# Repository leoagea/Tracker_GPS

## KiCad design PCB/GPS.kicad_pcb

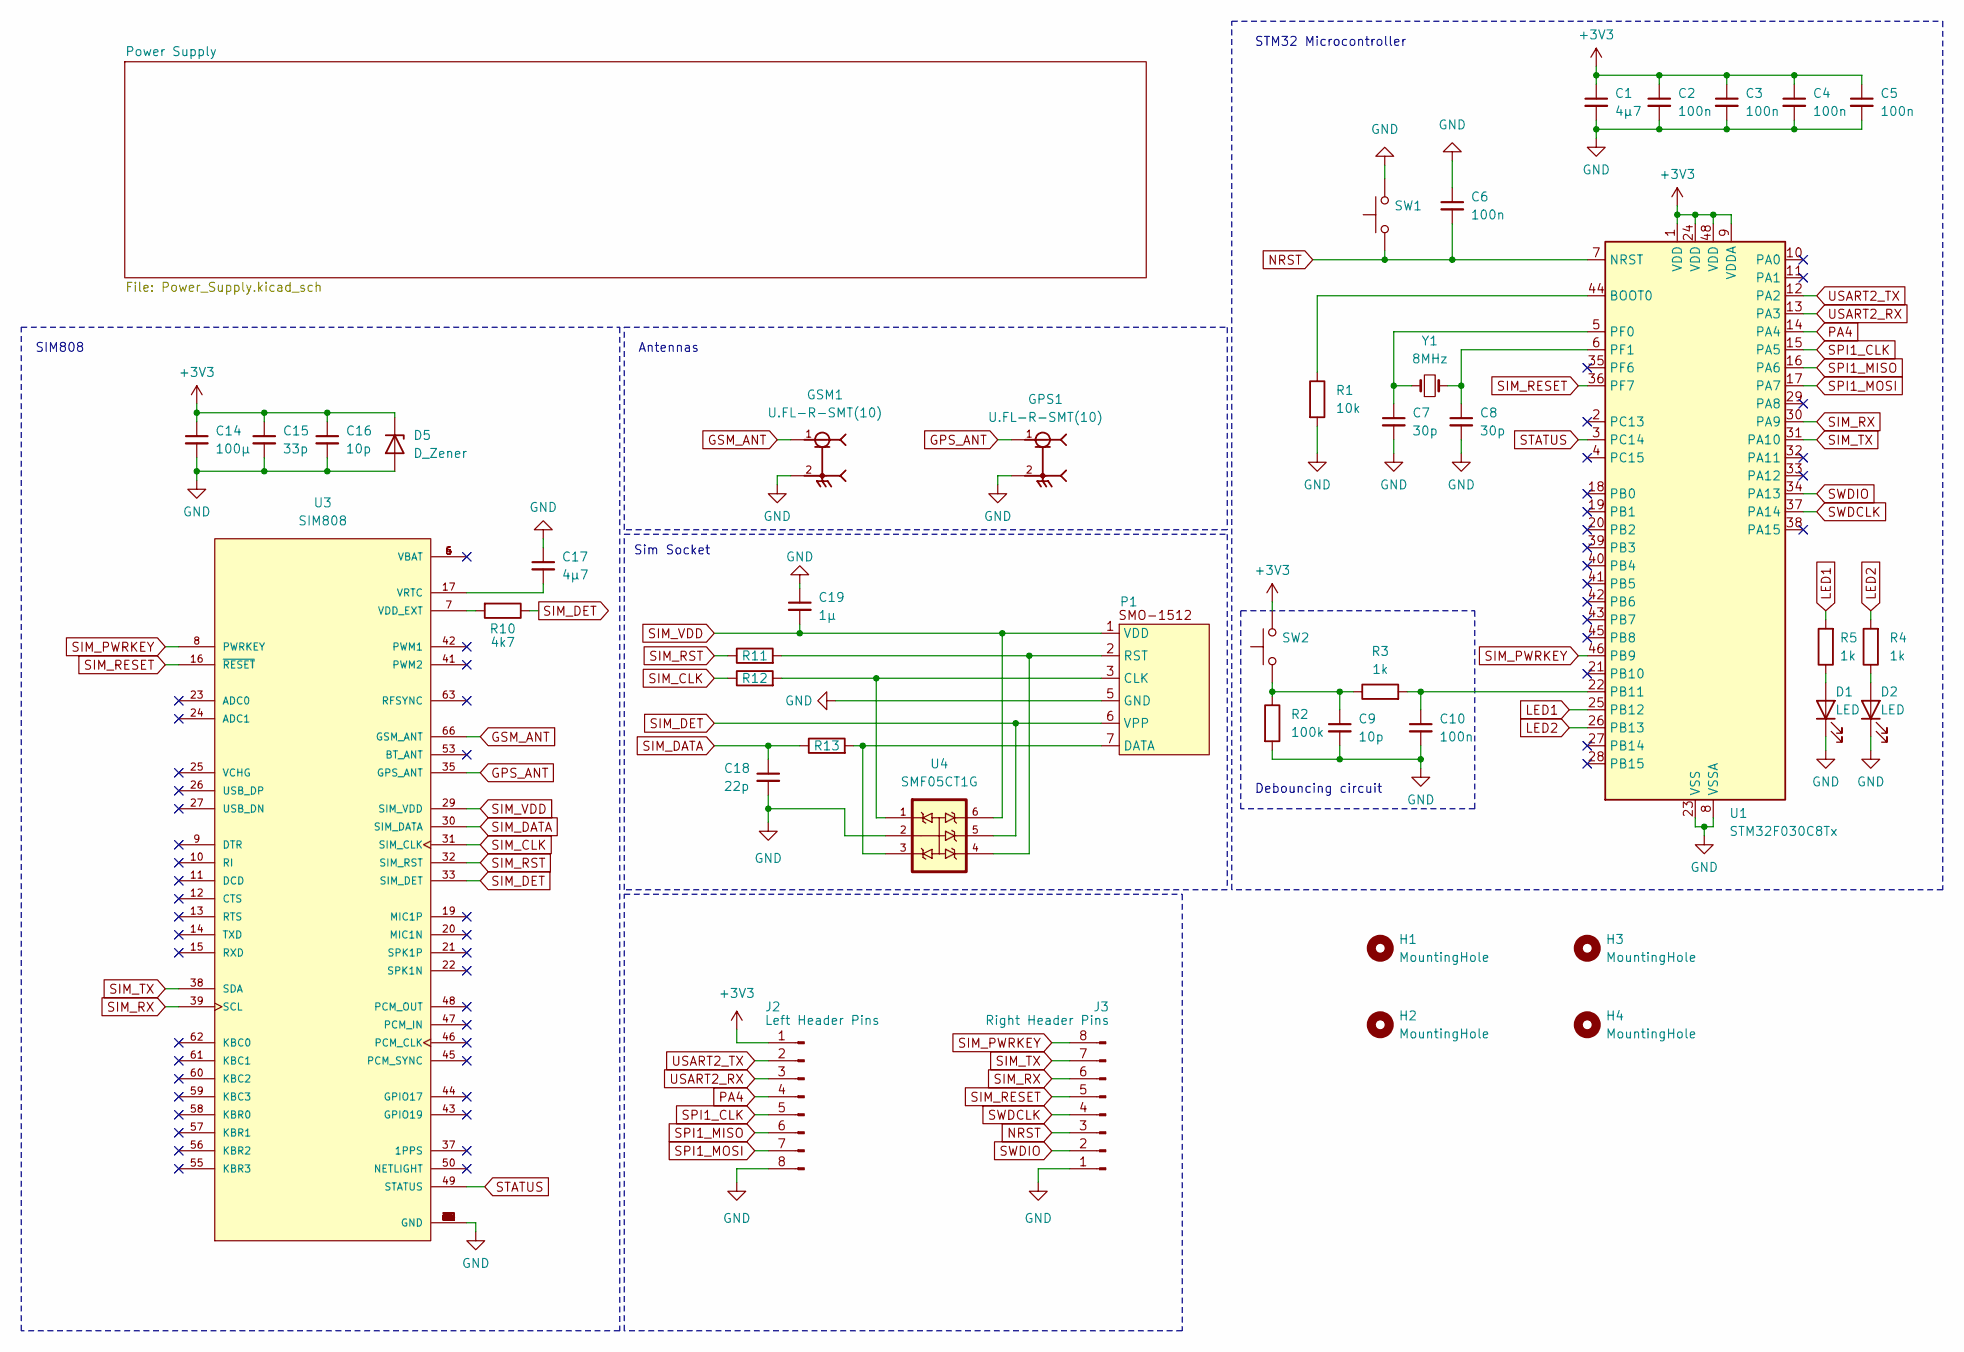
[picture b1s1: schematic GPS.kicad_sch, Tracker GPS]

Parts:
C1, C17: 4µ7; C_0603_1608Metric_Pad1.08x0.95mm_HandSolder; LCSC C19666
C2, C3, C4, C5, C6, C10: 100n; C_0402_1005Metric_Pad0.74x0.62mm_HandSolder; LCSC C1525
C7, C8: 30p; C_0402_1005Metric_Pad0.74x0.62mm_HandSolder; LCSC C1570
C9, C16: 10p; C_0402_1005Metric_Pad0.74x0.62mm_HandSolder; LCSC C32949
C14: 100µ; C_1206_3216Metric_Pad1.33x1.80mm_HandSolder; LCSC C15008
C15: 33p; C_0402_1005Metric_Pad0.74x0.62mm_HandSolder; LCSC C1562
C18: 22p; C_0402_1005Metric_Pad0.74x0.62mm_HandSolder; LCSC C1555
C19: 1µ; C_0402_1005Metric_Pad0.74x0.62mm_HandSolder; LCSC C52923
D1: LED; LED_0603_1608Metric_Pad1.05x0.95mm_HandSolder; LCSC C5151484
D2: LED; LED_0603_1608Metric_Pad1.05x0.95mm_HandSolder; LCSC C2286
D5: D_Zener; D_MiniMELF_Handsoldering; LCSC C2857190
GPS1: U.FL-R-SMT(10); U.FL_Hirose_U.FL-R-SMT-1_Vertical; LCSC C88373
GSM1: U.FL-R-SMT(10); U.FL_Hirose_U.FL-R-SMT-1_Vertical; LCSC C88373
H1, H2, H3, H4: MountingHole; MountingHole_2.5mm_Pad_Via
J2: Left Header Pins; PinHeader_1x08_P2.54mm_Vertical
J3: Right Header Pins; PinHeader_1x08_P2.54mm_Vertical
P1: SIM_CARD_SMO-1512; LCSC C125621
R1: 10k; R_01005_0402Metric_Pad0.57x0.30mm_HandSolder; LCSC C25744
R2: 100k; R_0201_0603Metric_Pad0.64x0.40mm_HandSolder; LCSC C25803
R3, R4, R5: 1k; R_0201_0603Metric_Pad0.64x0.40mm_HandSolder; LCSC C21190
R10: 4k7; R_0402_1005Metric_Pad0.72x0.64mm_HandSolder; LCSC C25900
R11, R12, R13: 22; R_01005_0402Metric_Pad0.57x0.30mm_HandSolder; LCSC C25092
SW1, SW2: SW_Push; XKB-TS-1187A; LCSC C318884
U1: STM32F030C8Tx; LQFP-48_7x7mm_P0.5mm; LCSC C23922
U3: SIM808; PARTREV 1.03; LCSC C126275
U4: SMF05CT1G; SOT-363_SC-70-6_Handsoldering; LCSC C15879
Y1: 8MHz; Crystal_SMD_5032-2Pin_5.0x3.2mm_HandSoldering; LCSC C115962

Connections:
+3V3: C1.1, C2.1, C3.1, C4.1, C5.1, C14.1, C15.1, C16.1, D5.1 (K), J2.1, SW2.2, U1.1 (VDD), U1.9 (VDDA), U1.24 (VDD), U1.48 (VDD); also elsewhere on the board
GND: C1.2, C2.2, C3.2, C4.2, C5.2, C6.1, C7.2, C8.2, C9.2, C10.2, C14.2, C15.2, C16.2, C17.1, C18.2, C19.1, D1.1 (K), D2.1 (K), D5.2 (A), GPS1.2, GSM1.2, J2.8, J3.1, P1.5 (GND), R1.2, R2.2, SW1.2, U1.8 (VSSA), U1.23 (VSS), U1.47 (VSS), U3.1 (GND), U3.2 (GND), U3.3 (GND), U3.18 (GND), U3.28 (GND), U3.34 (GND), U3.36 (GND), U3.40 (GND), U3.51 (GND), U3.52 (GND), U3.54 (GND), U3.64 (GND), U3.65 (GND), U3.67 (GND), U3.68 (GND), U4.2; also elsewhere on the board
GPS_ANT: GPS1.1, U3.35 (GPS_ANT)
GSM_ANT: GSM1.1, U3.66 (GSM_ANT)
LED1: R5.2, U1.25 (PB12)
LED2: R4.2, U1.26 (PB13)
NRST: C6.2, J3.3, SW1.1, U1.7 (NRST)
unnamed: C9.1, R2.1, R3.1, SW2.1
unnamed: D1.2 (A), R5.1
unnamed: D2.2 (A), R4.1
unnamed: P1.3 (CLK), R12.2, U4.1
unnamed: P1.7 (DATA), R13.2, U4.3
unnamed: P1.2 (RST), R11.2, U4.4
unnamed: R1.1, U1.44 (BOOT0)
unnamed: C10.1, R3.2, U1.22 (PB11)
unnamed: C7.1, U1.5 (PF0), Y1.1
unnamed: C8.1, U1.6 (PF1), Y1.2
unnamed: R10.2, U3.7 (VDD_EXT)
unnamed: C17.2, U3.17 (VRTC)
PA4: J2.4, U1.14 (PA4)
SIM_CLK: R12.1, U3.31 (SIM_CLK)
SIM_DATA: C18.1, R13.1, U3.30 (SIM_DATA)
SIM_DET: P1.6 (VPP), R10.1, U3.33 (SIM_DET), U4.5
SIM_PWRKEY: J3.8, U1.46 (PB9), U3.8 (PWRKEY)
SIM_RESET: J3.5, U1.36 (PF7), U3.16 (~RESET)
SIM_RST: R11.1, U3.32 (SIM_RST)
SIM_RX: J3.6, U1.30 (PA9), U3.39 (SCL)
SIM_TX: J3.7, U1.31 (PA10), U3.38 (SDA)
SIM_VDD: C19.2, P1.1 (VDD), U3.29 (SIM_VDD), U4.6
SPI1_CLK: J2.5, U1.15 (PA5)
SPI1_MISO: J2.6, U1.16 (PA6)
SPI1_MOSI: J2.7, U1.17 (PA7)
STATUS: U1.3 (PC14), U3.49 (STATUS)
SWDCLK: J3.4, U1.37 (PA14)
SWDIO: J3.2, U1.34 (PA13)
USART2_RX: J2.3, U1.13 (PA3)
USART2_TX: J2.2, U1.12 (PA2)

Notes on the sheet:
Antennas
Sim Socket
Debouncing circuit
SIM808
STM32 Microcontroller

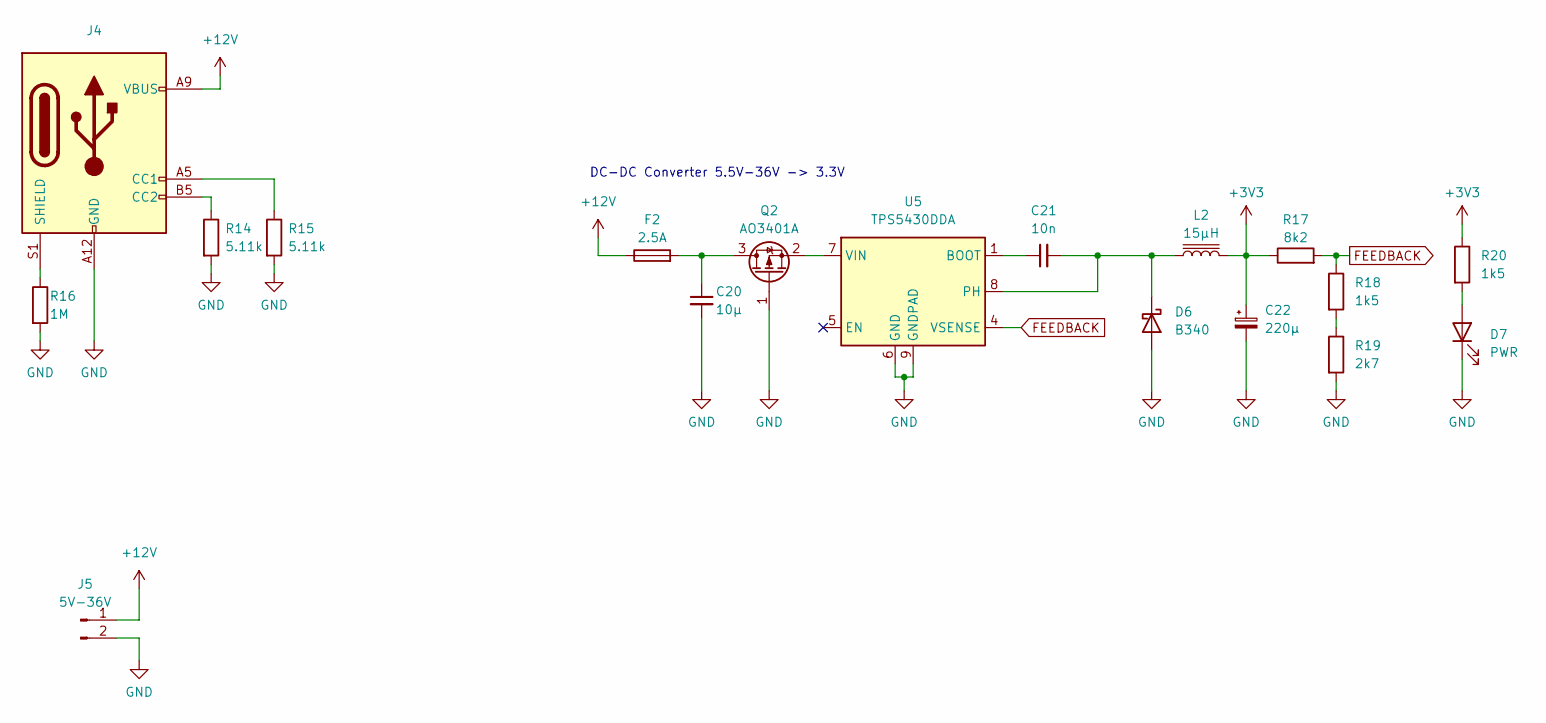
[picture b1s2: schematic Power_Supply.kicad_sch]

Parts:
C20: 10µ; C_0805_2012Metric_Pad1.18x1.45mm_HandSolder; LCSC C15850
C21: 10n; C_0805_2012Metric_Pad1.18x1.45mm_HandSolder; LCSC C1710
C22: 220µ; CP_EIA-7343-15_Kemet-W_Pad2.25x2.55mm_HandSolder; LCSC C242173
D6: B340; D_SMA_Handsoldering; LCSC C64982
D7: PWR; LED_0603_1608Metric_Pad1.05x0.95mm_HandSolder; LCSC C2286
F2: 2.5A; Fuse_0402_1005Metric_Pad0.77x0.64mm_HandSolder; LCSC C311046
J4: USB_C_Receptacle_PowerOnly_6P; USB_C_Receptacle_GCT_USB4125-xx-x-0190_6P_TopMnt_Horizontal; LCSC C668623
J5: 5V-36V; PinHeader_1x02_P2.54mm_Vertical
L2: 15µH; L_TechFuse_SL0630; LCSC C22463824
Q2: AO3401A; SOT-23W_Handsoldering; LCSC C2938376
R14, R15: 5.11k; R_0402_1005Metric_Pad0.72x0.64mm_HandSolder; LCSC C5126228
R16: 1M; R_0402_1005Metric_Pad0.72x0.64mm_HandSolder; LCSC C2906900
R17: 8k2; R_0805_2012Metric_Pad1.20x1.40mm_HandSolder; LCSC C17828
R18, R20: 1k5; R_0805_2012Metric_Pad1.20x1.40mm_HandSolder; LCSC C4310
R19: 2k7; R_0805_2012Metric_Pad1.20x1.40mm_HandSolder; LCSC C17530
U5: TPS5430DDA; TI_SO-PowerPAD-8_ThermalVias; LCSC C9864

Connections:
+3V3: C22.1, L2.2, R17.1, R20.1; also elsewhere on the board
+12V: F2.1, J4.A9 (VBUS), J4.B9 (VBUS), J5.1
FEEDBACK: R17.2, R18.1, U5.4 (VSENSE)
GND: C20.2, C22.2, D6.2 (A), D7.1 (K), J4.A12 (GND), J4.B12 (GND), J5.2, Q2.1 (G), R14.2, R15.2, R16.2, R19.2, U5.6 (GND), U5.9 (GNDPAD); also elsewhere on the board
unnamed: C21.2, D6.1 (K), L2.1, U5.8 (PH)
unnamed: D7.2 (A), R20.2
unnamed: J4.A5 (CC1), R15.1
unnamed: J4.B5 (CC2), R14.1
unnamed: J4.S1 (SHIELD), R16.1
unnamed: C20.1, F2.2, Q2.3 (D)
unnamed: Q2.2 (S), U5.7 (VIN)
unnamed: R18.2, R19.1
unnamed: C21.1, U5.1 (BOOT)

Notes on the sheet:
DC-DC Converter 5.5V-36V -> 3.3V

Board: 2 copper layers, 61 parts (0 on the bottom side), 48 nets, no tracks yet.

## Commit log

2024-11-12 Add: Schematic V1
2024-11-27 Add footprint for all elements
